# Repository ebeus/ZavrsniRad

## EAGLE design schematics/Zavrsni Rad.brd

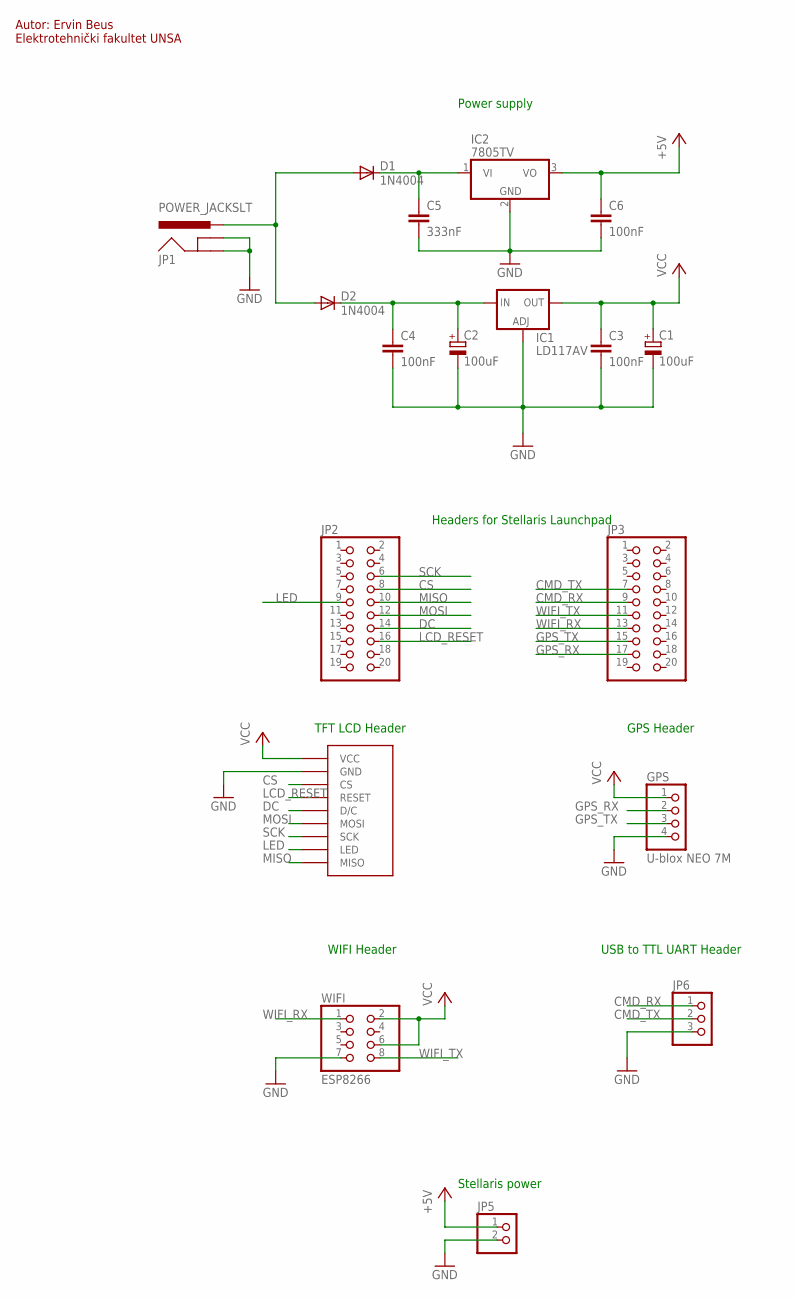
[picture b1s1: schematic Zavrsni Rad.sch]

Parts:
C1, C2: 100uF; E2,5-6E
C3, C4, C6: 100nF; C025-024X044
C5: 333nF; C025-024X044
D1, D2: 1N4004; DO41-10
GPS: U-blox NEO 7M; 1X04
IC1: LD117AV; TO220L1
IC2: 7805TV; TO220V
JP1: POWER_JACKSLT; POWER_JACK_SLOT
JP2, JP3: PINHD-2X10; 2X10
JP5: PINHD-1X2; 1X02
JP6: PINHD-1X3; 1X03
TFTLCD: SPI_TFT_DISPLAY; SPI_DISPLAY
WIFI: ESP8266; 2X04

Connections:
+5V: C6.1, IC2.3 (VO), JP5.1
CMD_RX: JP3.9, JP6.1
CMD_TX: JP3.7, JP6.2
CS: JP2.8, TFTLCD.CS
DC: JP2.14, TFTLCD.D/C
GND: C1.-, C2.-, C3.2, C4.2, C5.2, C6.2, GPS.4, IC1.1 (ADJ), IC2.2 (GND), JP1.GND@1 (GNDBREAK), JP1.GND@2 (GND), JP5.2, JP6.3, TFTLCD.GND, WIFI.7
GPS_RX: GPS.2, JP3.17
GPS_TX: GPS.3, JP3.15
LCD_RESET: JP2.16, TFTLCD.RESET
LED: JP2.9, TFTLCD.LED
MISO: JP2.10, TFTLCD.MISO
MOSI: JP2.12, TFTLCD.MOSI
unnamed: C5.1, D1.C, IC2.1 (VI)
unnamed: D1.A, D2.A, JP1.PWR
unnamed: C2.+, C4.1, D2.C, IC1.3 (IN)
SCK: JP2.6, TFTLCD.SCK
VCC: C1.+, C3.1, GPS.1, IC1.2 (OUT), TFTLCD.VCC, WIFI.2, WIFI.6
WIFI_RX: JP3.13, WIFI.1
WIFI_TX: JP3.11, WIFI.8

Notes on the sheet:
Headers for Stellaris Launchpad
Power supply
GPS Header
WIFI Header
TFT LCD Header
USB to TTL UART Header
Stellaris power
Autor: Ervin Beus Elektrotehnički fakultet UNSA

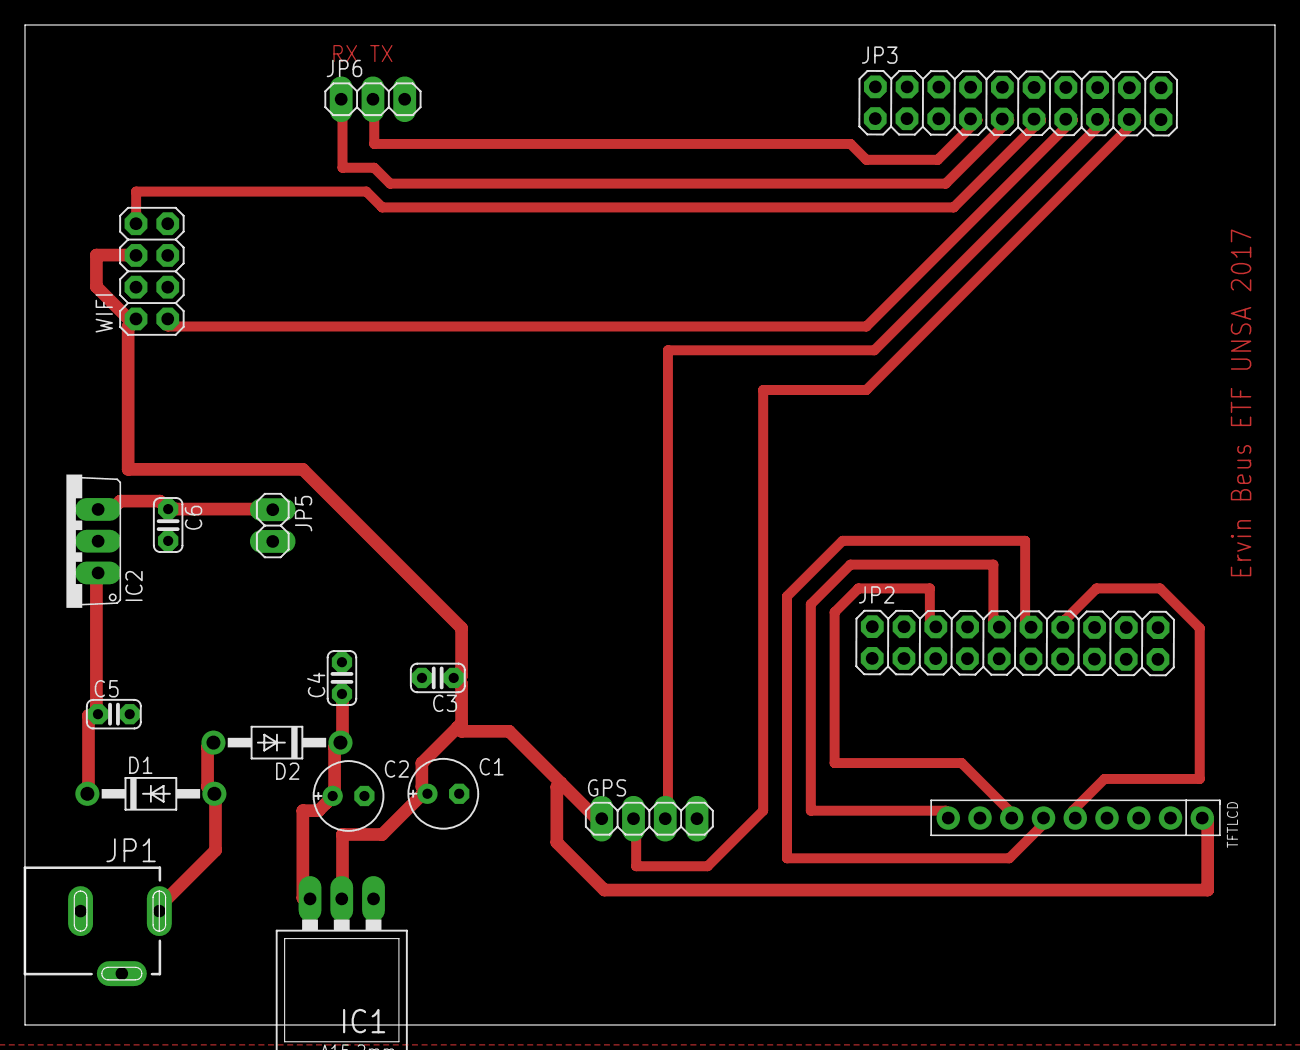
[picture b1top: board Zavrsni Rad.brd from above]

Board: 2 copper layers, 100.0 x 80.0 mm, 18 parts (0 on the bottom side), 19 nets.
